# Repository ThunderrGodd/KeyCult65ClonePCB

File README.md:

# KeyCult65ClonePCB
 An opensource version of keycult no.2/65 pcb
 
 BackSpace Split / 6.25U or 7U Spacebar / CapsLock Indicator
 
 Prebuilt Firmware file, Flash it for VIA

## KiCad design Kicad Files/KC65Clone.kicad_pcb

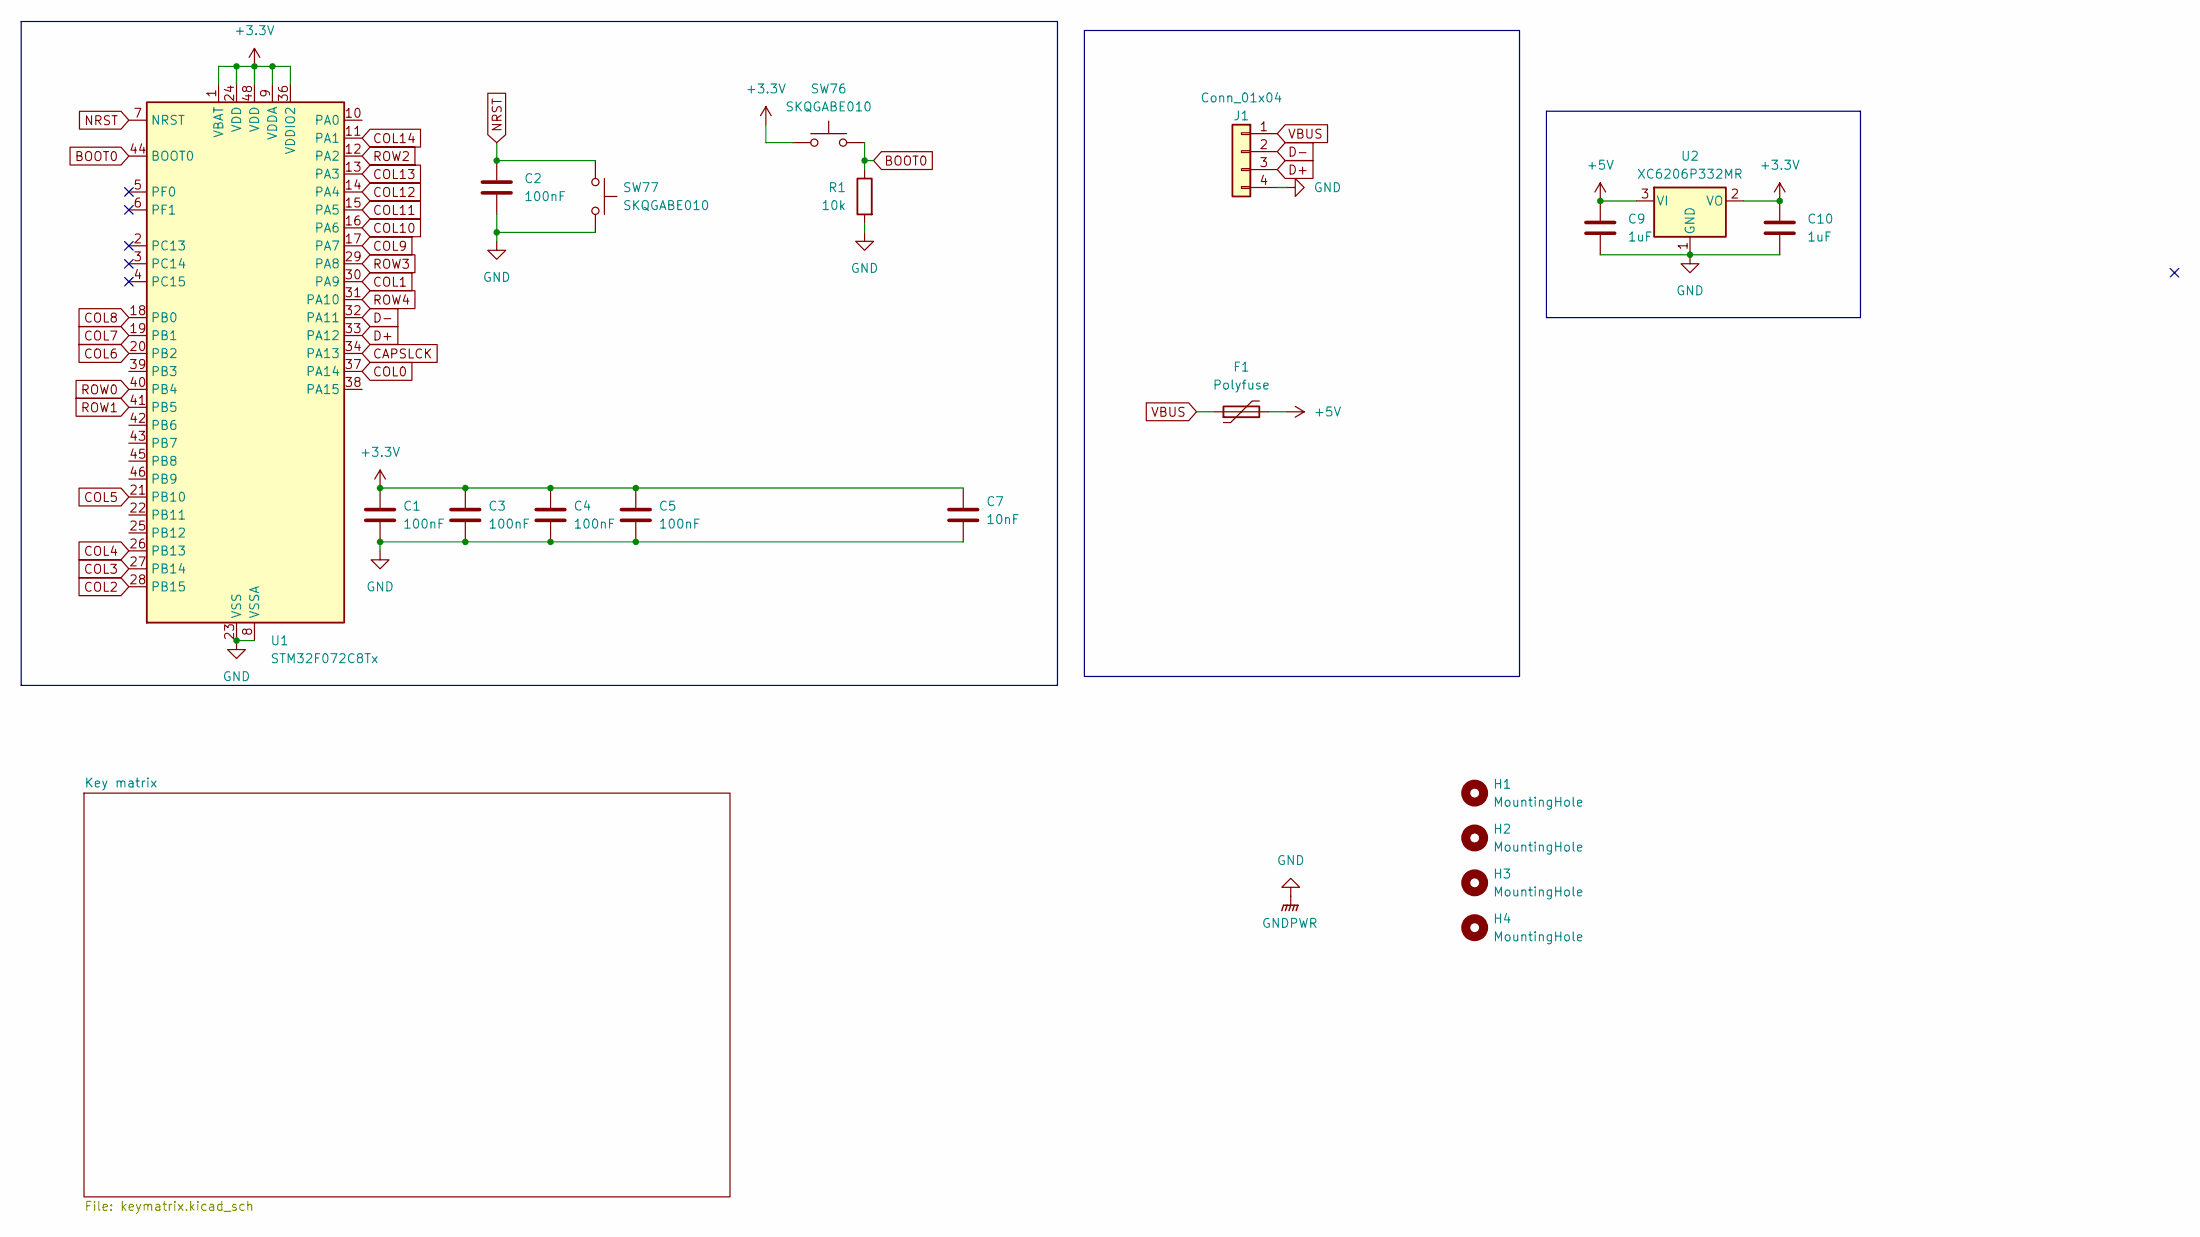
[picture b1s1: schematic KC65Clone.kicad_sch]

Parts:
C1, C2, C3, C4, C5: 100nF; C_0402_1005Metric
C7: 10nF; C_0402_1005Metric
C9, C10: 1uF; C_0603_1608Metric
F1: Polyfuse; Fuse_1206_3216Metric
H1, H2, H3, H4: MountingHole; MountingHole_3.5mm
J1: Conn_01x04; JST_SH_SM04B-SRSS-TB_1x04-1MP_P1.00mm_Horizontal
R1: 10k; R_0402_1005Metric
SW76, SW77: SKQGABE010; SW_SPST_SKQG_WithoutStem
U1: STM32F072C8Tx; LQFP-48_7x7mm_P0.5mm
U2: XC6206P332MR; SOT-23-3

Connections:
+3.3V: C1.1, C3.1, C4.1, C5.1, C7.1, C10.1, SW76.1, U1.1 (VBAT), U1.9 (VDDA), U1.24 (VDD), U1.36 (VDDIO2), U1.48 (VDD), U2.2 (VO)
+5V: C9.1, F1.2, U2.3 (VI)
BOOT0: R1.1, SW76.2, U1.44 (BOOT0)
CAPSLCK: U1.34 (PA13); also elsewhere on the board
COL0: U1.37 (PA14); also elsewhere on the board
COL1: U1.30 (PA9); also elsewhere on the board
COL2: U1.28 (PB15); also elsewhere on the board
COL3: U1.27 (PB14); also elsewhere on the board
COL4: U1.26 (PB13); also elsewhere on the board
COL5: U1.21 (PB10); also elsewhere on the board
COL6: U1.20 (PB2); also elsewhere on the board
COL7: U1.19 (PB1); also elsewhere on the board
COL8: U1.18 (PB0); also elsewhere on the board
COL9: U1.17 (PA7); also elsewhere on the board
COL10: U1.16 (PA6); also elsewhere on the board
COL11: U1.15 (PA5); also elsewhere on the board
COL12: U1.14 (PA4); also elsewhere on the board
COL13: U1.13 (PA3); also elsewhere on the board
COL14: U1.11 (PA1); also elsewhere on the board
D+: J1.3, U1.33 (PA12)
D-: J1.2, U1.32 (PA11)
GND: C1.2, C2.2, C3.2, C4.2, C5.2, C7.2, C9.2, C10.2, J1.4, R1.2, SW77.2, U1.8 (VSSA), U1.23 (VSS), U1.35 (VSS), U1.47 (VSS), U2.1 (GND); also elsewhere on the board
NRST: C2.1, SW77.1, U1.7 (NRST)
ROW0: U1.40 (PB4); also elsewhere on the board
ROW1: U1.41 (PB5); also elsewhere on the board
ROW2: U1.12 (PA2); also elsewhere on the board
ROW3: U1.29 (PA8); also elsewhere on the board
ROW4: U1.31 (PA10); also elsewhere on the board
VBUS: F1.1, J1.1

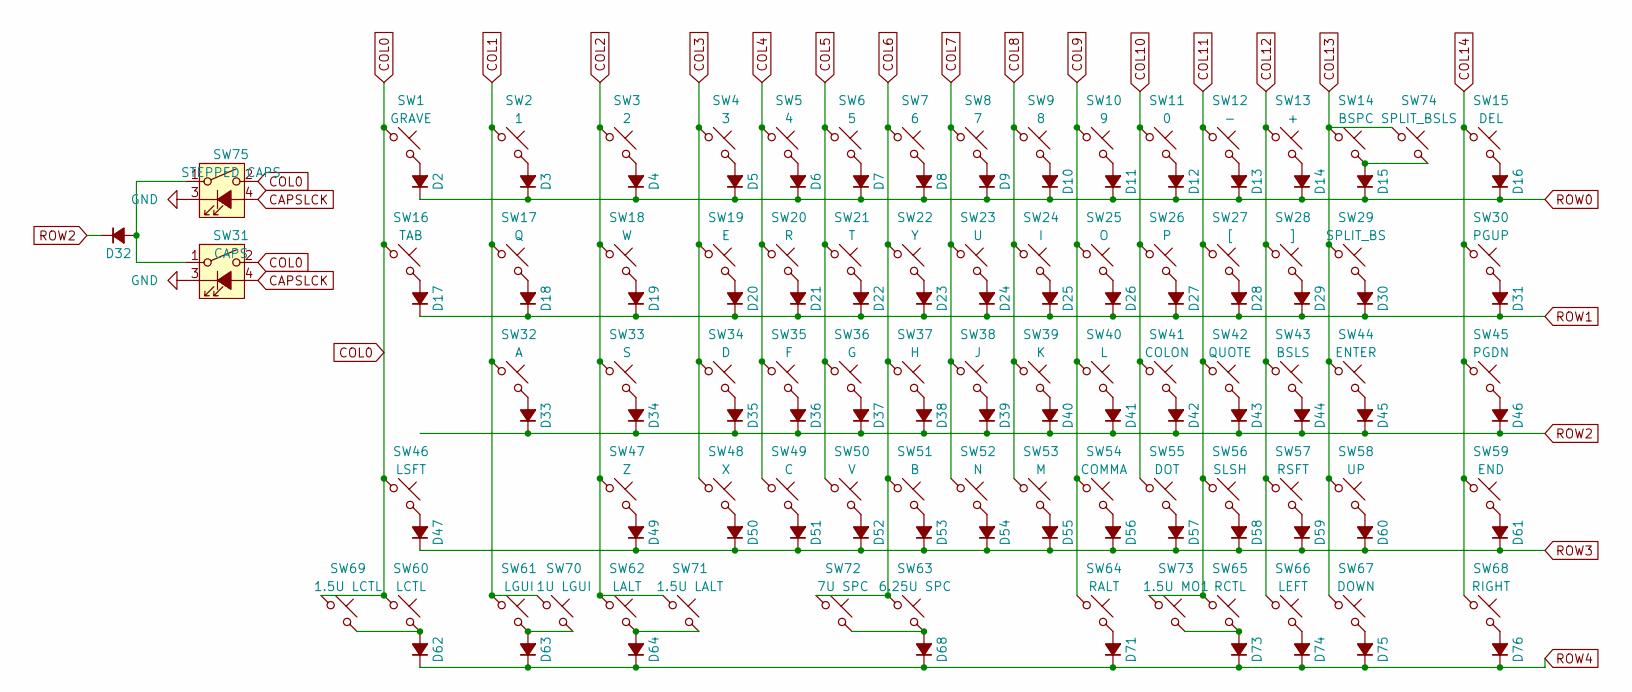
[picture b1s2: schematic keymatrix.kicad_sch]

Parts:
D2, D3, D4, D5, D6, D7, D8, D9, D10, D11, D12, D13, D14, D15, D16, D17, D18, D19, D20, D21, D22, D23, D24, D25, D26, D27, D28, D29, D30, D31, D32, D33, D34, D35, D36, D37, D38, D39, D40, D41, D42, D43, D44, D45, D46, D47, D49, D50, D51, D52, D53, D54, D55, D56, D57, D58, D59, D60, D61, D62, D63, D64, D68, D71, D73, D74, D75, D76: D_Small_Filled; D_SOD-123
SW1: GRAVE; CherryMX_1.00u_PCB
SW2: 1; CherryMX_1.00u_PCB
SW3: 2; CherryMX_1.00u_PCB
SW4: 3; CherryMX_1.00u_PCB
SW5: 4; CherryMX_1.00u_PCB
SW6: 5; CherryMX_1.00u_PCB
SW7: 6; CherryMX_1.00u_PCB
SW8: 7; CherryMX_1.00u_PCB
SW9: 8; CherryMX_1.00u_PCB
SW10: 9; CherryMX_1.00u_PCB
SW11: 0; CherryMX_1.00u_PCB
SW12: -; CherryMX_1.00u_PCB
SW13: +; CherryMX_1.00u_PCB
SW14: BSPC; CherryMX_2.00u_PCB_StabWireBottom
SW15: DEL; CherryMX_1.00u_PCB
SW16: TAB; CherryMX_1.50u_PCB
SW17: Q; CherryMX_1.00u_PCB
SW18: W; CherryMX_1.00u_PCB
SW19: E; CherryMX_1.00u_PCB
SW20: R; CherryMX_1.00u_PCB
SW21: T; CherryMX_1.00u_PCB
SW22: Y; CherryMX_1.00u_PCB
SW23: U; CherryMX_1.00u_PCB
SW24: I; CherryMX_1.00u_PCB
SW25: O; CherryMX_1.00u_PCB
SW26: P; CherryMX_1.00u_PCB
SW27: [; CherryMX_1.00u_PCB
SW28: ]; CherryMX_1.00u_PCB
SW29: SPLIT_BS; CherryMX_1.00u_PCB
SW30: PGUP; CherryMX_1.00u_PCB
SW31: CAPS; CherryMX_1.75u_PCB
SW32: A; CherryMX_1.00u_PCB
SW33: S; CherryMX_1.00u_PCB
SW34: D; CherryMX_1.00u_PCB
SW35: F; CherryMX_1.00u_PCB
SW36: G; CherryMX_1.00u_PCB
SW37: H; CherryMX_1.00u_PCB
SW38: J; CherryMX_1.00u_PCB
SW39: K; CherryMX_1.00u_PCB
SW40: L; CherryMX_1.00u_PCB
SW41: COLON; CherryMX_1.00u_PCB
SW42: QUOTE; CherryMX_1.00u_PCB
SW43: BSLS; CherryMX_1.50u_PCB
SW44: ENTER; CherryMX_2.25u_PCB_StabWireBottom
SW45: PGDN; CherryMX_1.00u_PCB
SW46: LSFT; CherryMX_2.25u_PCB_StabWireBottom
SW47: Z; CherryMX_1.00u_PCB
SW48: X; CherryMX_1.00u_PCB
SW49: C; CherryMX_1.00u_PCB
SW50: V; CherryMX_1.00u_PCB
SW51: B; CherryMX_1.00u_PCB
SW52: N; CherryMX_1.00u_PCB
SW53: M; CherryMX_1.00u_PCB
SW54: COMMA; CherryMX_1.00u_PCB
SW55: DOT; CherryMX_1.00u_PCB
SW56: SLSH; CherryMX_1.00u_PCB
SW57: RSFT; CherryMX_1.75u_PCB
SW58: UP; CherryMX_1.00u_PCB
SW59: END; CherryMX_1.00u_PCB
SW60: LCTL; CherryMX_1.25u_PCB
SW61: LGUI; CherryMX_1.25u_PCB
SW62: LALT; CherryMX_1.25u_PCB
SW63: 6.25U SPC; CherryMX_6.25u_PCB_StabWireTop
SW64: RALT; CherryMX_1.25u_PCB
SW65: RCTL; CherryMX_1.25u_PCB
SW66: LEFT; CherryMX_1.00u_PCB
SW67: DOWN; CherryMX_1.00u_PCB
SW68: RIGHT; CherryMX_1.00u_PCB
SW69: 1.5U LCTL; CherryMX_1.50u_PCB
SW70: 1U LGUI; CherryMX_1.00u_PCB
SW71: 1.5U LALT; CherryMX_1.50u_PCB
SW72: 7U SPC; CherryMX_7.00u_PCB_StabWireTop
SW73: 1.5U MO1; CherryMX_1.50u_PCB
SW74: SPLIT_BSLS; CherryMX_1.00u_PCB
SW75: STEPPED CAPS; CherryMX_1.25u_PCB

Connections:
CAPSLCK: SW31.4 (A), SW75.4 (A); also elsewhere on the board
COL0: SW1.2, SW16.2, SW31.2, SW46.2, SW60.2, SW69.2, SW75.2; also elsewhere on the board
COL1: SW2.2, SW17.2, SW32.2, SW61.2, SW70.2; also elsewhere on the board
COL2: SW3.2, SW18.2, SW33.2, SW47.2, SW62.2, SW71.2; also elsewhere on the board
COL3: SW4.2, SW19.2, SW34.2, SW48.2; also elsewhere on the board
COL4: SW5.2, SW20.2, SW35.2, SW49.2; also elsewhere on the board
COL5: SW6.2, SW21.2, SW36.2, SW50.2; also elsewhere on the board
COL6: SW7.2, SW22.2, SW37.2, SW51.2, SW63.2, SW72.2; also elsewhere on the board
COL7: SW8.2, SW23.2, SW38.2, SW52.2; also elsewhere on the board
COL8: SW9.2, SW24.2, SW39.2, SW53.2; also elsewhere on the board
COL9: SW10.2, SW25.2, SW40.2, SW54.2, SW64.2; also elsewhere on the board
COL10: SW11.2, SW26.2, SW41.2, SW55.2; also elsewhere on the board
COL11: SW12.2, SW27.2, SW42.2, SW56.2, SW65.2, SW73.2; also elsewhere on the board
COL12: SW13.2, SW28.2, SW43.2, SW57.2, SW66.2; also elsewhere on the board
COL13: SW14.2, SW29.2, SW44.2, SW58.2, SW67.2, SW74.2; also elsewhere on the board
COL14: SW15.2, SW30.2, SW45.2, SW59.2, SW68.2; also elsewhere on the board
GND: SW31.3 (K), SW75.3 (K); also elsewhere on the board
unnamed: D2.2 (A), SW1.1
unnamed: D3.2 (A), SW2.1
unnamed: D4.2 (A), SW3.1
unnamed: D5.2 (A), SW4.1
unnamed: D6.2 (A), SW5.1
unnamed: D7.2 (A), SW6.1
unnamed: D8.2 (A), SW7.1
unnamed: D9.2 (A), SW8.1
unnamed: D10.2 (A), SW9.1
unnamed: D11.2 (A), SW10.1
unnamed: D12.2 (A), SW11.1
unnamed: D13.2 (A), SW12.1
unnamed: D14.2 (A), SW13.1
unnamed: D15.2 (A), SW14.1, SW74.1
unnamed: D16.2 (A), SW15.1
unnamed: D17.2 (A), SW16.1
unnamed: D18.2 (A), SW17.1
unnamed: D19.2 (A), SW18.1
unnamed: D20.2 (A), SW19.1
unnamed: D21.2 (A), SW20.1
unnamed: D22.2 (A), SW21.1
unnamed: D23.2 (A), SW22.1
unnamed: D24.2 (A), SW23.1
unnamed: D25.2 (A), SW24.1
unnamed: D26.2 (A), SW25.1
unnamed: D27.2 (A), SW26.1
unnamed: D28.2 (A), SW27.1
unnamed: D29.2 (A), SW28.1
unnamed: D30.2 (A), SW29.1
unnamed: D31.2 (A), SW30.1
unnamed: D32.2 (A), SW31.1, SW75.1
unnamed: D33.2 (A), SW32.1
unnamed: D34.2 (A), SW33.1
unnamed: D35.2 (A), SW34.1
unnamed: D36.2 (A), SW35.1
unnamed: D37.2 (A), SW36.1
unnamed: D38.2 (A), SW37.1
unnamed: D39.2 (A), SW38.1
unnamed: D40.2 (A), SW39.1
unnamed: D41.2 (A), SW40.1
unnamed: D42.2 (A), SW41.1
unnamed: D43.2 (A), SW42.1
unnamed: D44.2 (A), SW43.1
unnamed: D45.2 (A), SW44.1
unnamed: D46.2 (A), SW45.1
unnamed: D47.2 (A), SW46.1
unnamed: D49.2 (A), SW47.1
unnamed: D50.2 (A), SW48.1
unnamed: D51.2 (A), SW49.1
unnamed: D52.2 (A), SW50.1
unnamed: D53.2 (A), SW51.1
unnamed: D54.2 (A), SW52.1
unnamed: D55.2 (A), SW53.1
unnamed: D56.2 (A), SW54.1
unnamed: D57.2 (A), SW55.1
unnamed: D58.2 (A), SW56.1
unnamed: D59.2 (A), SW57.1
unnamed: D60.2 (A), SW58.1
unnamed: D61.2 (A), SW59.1
unnamed: D62.2 (A), SW60.1, SW69.1
unnamed: D63.2 (A), SW61.1, SW70.1
unnamed: D64.2 (A), SW62.1, SW71.1
unnamed: D68.2 (A), SW63.1, SW72.1
unnamed: D71.2 (A), SW64.1
unnamed: D73.2 (A), SW65.1, SW73.1
unnamed: D74.2 (A), SW66.1
unnamed: D75.2 (A), SW67.1
unnamed: D76.2 (A), SW68.1
ROW0: D2.1 (K), D3.1 (K), D4.1 (K), D5.1 (K), D6.1 (K), D7.1 (K), D8.1 (K), D9.1 (K), D10.1 (K), D11.1 (K), D12.1 (K), D13.1 (K), D14.1 (K), D15.1 (K), D16.1 (K); also elsewhere on the board
ROW1: D17.1 (K), D18.1 (K), D19.1 (K), D20.1 (K), D21.1 (K), D22.1 (K), D23.1 (K), D24.1 (K), D25.1 (K), D26.1 (K), D27.1 (K), D28.1 (K), D29.1 (K), D30.1 (K), D31.1 (K); also elsewhere on the board
ROW2: D32.1 (K), D33.1 (K), D34.1 (K), D35.1 (K), D36.1 (K), D37.1 (K), D38.1 (K), D39.1 (K), D40.1 (K), D41.1 (K), D42.1 (K), D43.1 (K), D44.1 (K), D45.1 (K), D46.1 (K); also elsewhere on the board
ROW3: D47.1 (K), D49.1 (K), D50.1 (K), D51.1 (K), D52.1 (K), D53.1 (K), D54.1 (K), D55.1 (K), D56.1 (K), D57.1 (K), D58.1 (K), D59.1 (K), D60.1 (K), D61.1 (K); also elsewhere on the board
ROW4: D62.1 (K), D63.1 (K), D64.1 (K), D68.1 (K), D71.1 (K), D73.1 (K), D74.1 (K), D75.1 (K), D76.1 (K); also elsewhere on the board

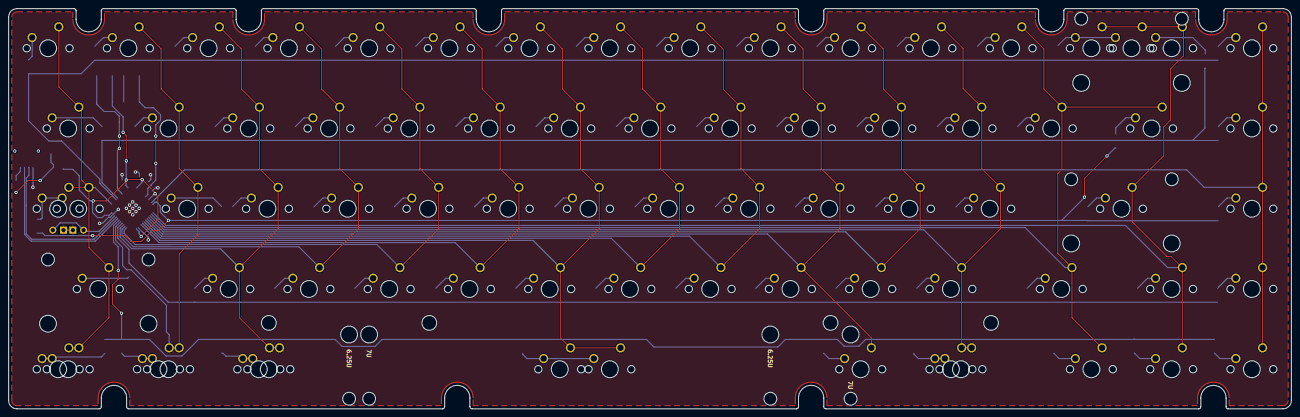
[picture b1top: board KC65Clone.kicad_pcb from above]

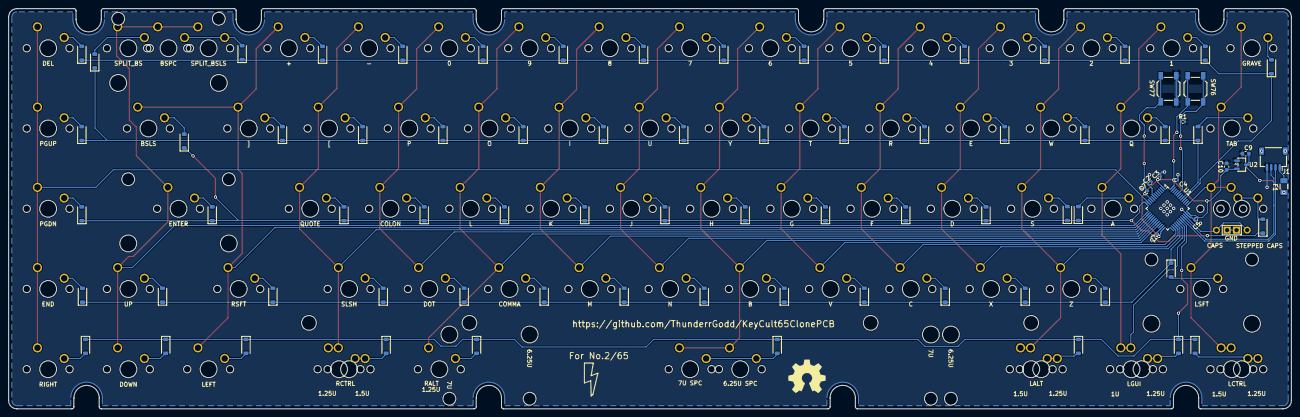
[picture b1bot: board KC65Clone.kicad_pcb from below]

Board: 2 copper layers, 304.5 x 95.0 mm, 162 parts (83 on the bottom side), 97 nets.

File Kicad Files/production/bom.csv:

Designator,Footprint,Quantity,Value,LCSC Part #
"C1, C2, C3, C4, C5, C8",0402,6,100nF,
"C10, C9",0603,2,1uF,
"C11, C12",0402,2,4.7uF,
C6,0402,1,1nF,
C7,0402,1,10nF,
D1,SOT-143,1,PRTR5V0U2X,
"D10, D11, D12, D13, D14, D15, D16, D17, D18, D19, D2, D20, D21, D22, D23, D24, D25, D26, D27, D28, D29, D3, D30, D31, D32, D33, D34, D35, D36, D37, D38, D39, D4, D40, D41, D42, D43, D44, D45, D46, D47, D49, D5, D50, D51, D52, D53, D54, D55, D56, D57, D58, D59, D6, D60, D61, D62, D63, D64, D68, D7, D71, D73, D74, D75, D76, D8, D9",D_SOD-123,68,D_Small_Filled,
F1,1206,1,Polyfuse,
J1,JST_SH_SM04B-SRSS-TB_1x04-1MP_P1.00mm_Horizontal,1,Conn_01x04,
R1,0402,1,10k,
SW1,CherryMX_1.00u_PCB,1,GRAVE,
SW10,CherryMX_1.00u_PCB,1,9,
SW11,CherryMX_1.00u_PCB,1,0,
SW12,CherryMX_1.00u_PCB,1,-,
SW13,CherryMX_1.00u_PCB,1,+,
SW14,CherryMX_2.00u_PCB_StabWireBottom,1,BSPC,
SW15,CherryMX_1.00u_PCB,1,DEL,
SW16,CherryMX_1.50u_PCB,1,TAB,
SW17,CherryMX_1.00u_PCB,1,Q,
SW18,CherryMX_1.00u_PCB,1,W,
SW19,CherryMX_1.00u_PCB,1,E,
SW2,CherryMX_1.00u_PCB,1,1,
SW20,CherryMX_1.00u_PCB,1,R,
SW21,CherryMX_1.00u_PCB,1,T,
SW22,CherryMX_1.00u_PCB,1,Y,
SW23,CherryMX_1.00u_PCB,1,U,
SW24,CherryMX_1.00u_PCB,1,I,
SW25,CherryMX_1.00u_PCB,1,O,
SW26,CherryMX_1.00u_PCB,1,P,
SW27,CherryMX_1.00u_PCB,1,[,
SW28,CherryMX_1.00u_PCB,1,],
SW29,CherryMX_1.00u_PCB,1,SPLIT_BS,
SW3,CherryMX_1.00u_PCB,1,2,
SW30,CherryMX_1.00u_PCB,1,PGUP,
SW31,CherryMX_1.75u_PCB_LED,1,CAPS,
SW32,CherryMX_1.00u_PCB,1,A,
SW33,CherryMX_1.00u_PCB,1,S,
SW34,CherryMX_1.00u_PCB,1,D,
SW35,CherryMX_1.00u_PCB,1,F,
SW36,CherryMX_1.00u_PCB,1,G,
SW37,CherryMX_1.00u_PCB,1,H,
SW38,CherryMX_1.00u_PCB,1,J,
SW39,CherryMX_1.00u_PCB,1,K,
SW4,CherryMX_1.00u_PCB,1,3,
SW40,CherryMX_1.00u_PCB,1,L,
SW41,CherryMX_1.00u_PCB,1,COLON,
SW42,CherryMX_1.00u_PCB,1,QUOTE,
SW43,CherryMX_1.50u_PCB,1,BSLS,
SW44,CherryMX_2.25u_PCB_StabWireBottom,1,ENTER,
SW45,CherryMX_1.00u_PCB,1,PGDN,
SW46,CherryMX_2.25u_PCB_StabWireBottom,1,LSFT,
SW47,CherryMX_1.00u_PCB,1,Z,
SW48,CherryMX_1.00u_PCB,1,X,
SW49,CherryMX_1.00u_PCB,1,C,
SW5,CherryMX_1.00u_PCB,1,4,
SW50,CherryMX_1.00u_PCB,1,V,
SW51,CherryMX_1.00u_PCB,1,B,
SW52,CherryMX_1.00u_PCB,1,N,
SW53,CherryMX_1.00u_PCB,1,M,
SW54,CherryMX_1.00u_PCB,1,COMMA,
SW55,CherryMX_1.00u_PCB,1,DOT,
SW56,CherryMX_1.00u_PCB,1,SLSH,
SW57,CherryMX_1.75u_PCB,1,RSFT,
SW58,CherryMX_1.00u_PCB,1,UP,
SW59,CherryMX_1.00u_PCB,1,END,
SW6,CherryMX_1.00u_PCB,1,5,
SW60,CherryMX_1.25u_PCB,1,LCTL,
SW61,CherryMX_1.25u_PCB,1,LGUI,
SW62,CherryMX_1.25u_PCB,1,LALT,
SW63,CherryMX_6.25u_PCB_StabWireTop,1,6.25U SPC,
SW64,CherryMX_1.25u_PCB,1,RALT,
SW65,CherryMX_1.25u_PCB,1,RCTL,
SW66,CherryMX_1.00u_PCB,1,LEFT,
SW67,CherryMX_1.00u_PCB,1,DOWN,
SW68,CherryMX_1.00u_PCB,1,RIGHT,
SW69,CherryMX_1.50u_PCB,1,1.5U LCTL,
SW7,CherryMX_1.00u_PCB,1,6,
SW70,CherryMX_1.00u_PCB,1,1U LGUI,
SW71,CherryMX_1.50u_PCB,1,1.5U LALT,
SW72,CherryMX_7.00u_PCB_StabWireTop,1,7U SPC,
SW73,CherryMX_1.50u_PCB,1,1.5U MO1,
SW74,CherryMX_1.00u_PCB,1,SPLIT_BSLS,
SW75,CherryMX_1.25u_PCB_LED,1,STEPPED CAPS,
"SW76, SW77",SW_SPST_SKQG_WithoutStem,2,SKQGABE010,
SW8,CherryMX_1.00u_PCB,1,7,
SW9,CherryMX_1.00u_PCB,1,8,
U1,LQFP-48_7x7mm_P0.5mm,1,STM32F072C8Tx,
U2,SOT-23-3,1,XC6206P332MR,

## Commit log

2025-04-17 added holes
2025-05-07 Edited BackSplit
2025-05-07 Updated Production Files
2026-03-31 deleted readme.md
2026-03-31 updated pcb
